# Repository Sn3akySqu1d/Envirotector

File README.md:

Envirotector is a compact, portable weather station that logs data to an SD card and displays temperature, air pressure and humidity data as well as the time on an OLED display.

I decided to make this project as a cool, portable way to track the conditions of different places you visit with the option to export the data via sd card for analysis.

Features:  
5 screens (time, temperature, humidity, air pressure, graph) that are navigaated using a rotary encoder  
Saves recorded data to an SD card every 10 minuites for up to 1 week 
Screen automaticlaly sleeps to save power  
The last screen has a graph that displays the sensor readings over time for the last 24 hours.

[BOM](BOM.csv)
# BOM  

| Component               | Link                                                                                                                                                                                                                                                                                                                                                                                                                                                                                                                                                                                                                                                                                                                                                                                                                                                                                                                                                                                                                                                                                                                                        | Component                  | Link                                                                                                           | Price (USD) |
| -------------------------- | -------------------------------------------------------------------------------------------------------------- | ----------- |
| XIAO RP2040                | [https://www.aliexpress.com/item/1005003682505451.html](https://www.aliexpress.com/item/1005003682505451.html) | 12.11       |
| DHT11 Humidity Sensor      | [https://www.aliexpress.com/item/1005007728845619.html](https://www.aliexpress.com/item/1005007728845619.html) | 5.02        |
| OLED Display               | [https://www.aliexpress.com/item/1005006262908701.html](https://www.aliexpress.com/item/1005006262908701.html) | 3.52        |
| RTC Module                 | [https://www.aliexpress.com/item/1005008352022059.html](https://www.aliexpress.com/item/1005008352022059.html) | 4.83        |
| BMP180 Air Pressure Sensor | [https://www.aliexpress.com/item/1005008474684719.html](https://www.aliexpress.com/item/1005008474684719.html) | 4.03        |
| Rotary Encoder             | [https://www.aliexpress.com/item/1975155185.html](https://www.aliexpress.com/item/1975155185.html)             | 3.62        |
| MicroSD Card Reader        | [https://www.aliexpress.com/item/1005006248599786.html](https://www.aliexpress.com/item/1005006248599786.html) | 2.39        |
| RTC Battery                | [https://www.aliexpress.com/item/1005008363279450.html](https://www.aliexpress.com/item/1005008363279450.html) | 5.90        |
| MicroSD Card               | [https://www.aliexpress.com/item/1005007118463161.html](https://www.aliexpress.com/item/1005007118463161.html) | 1.99        |
| PCB                        | [https://jlcpcb.com](https://jlcpcb.com)                                                                       | 1.50        |
| Case                       | Printed with my own 3D printer                                                                                 | 0.00        |
 total: 44.91 usd

https://youtu.be/wm6Xy655hNI?si=NdGpvTqHyldkWJcv

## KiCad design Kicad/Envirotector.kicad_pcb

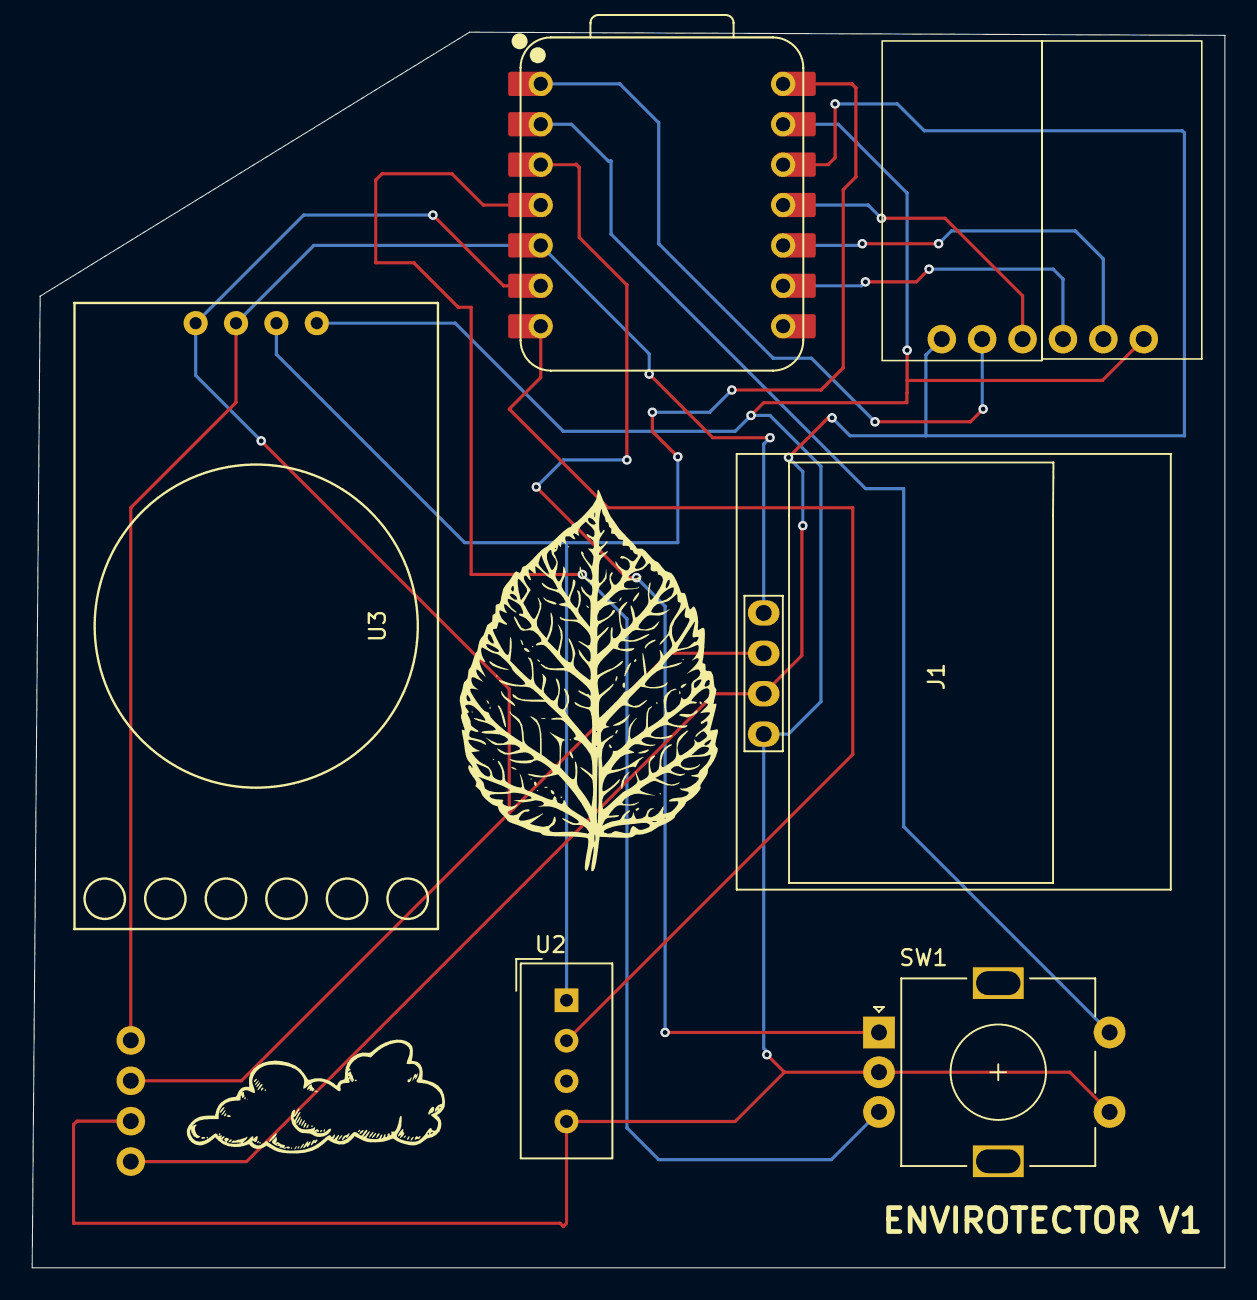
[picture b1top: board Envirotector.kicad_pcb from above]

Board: 2 copper layers, 75.0 x 77.7 mm, 7 parts (0 on the bottom side), 13 nets.

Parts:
J1: OLED Display; 128x64OLED
SW1: RotaryEncoder_Switch; RotaryEncoder_Alps_EC11E-Switch_Vertical_H20mm
U1: XIAO-RP2040-DIP
U2: DHT11; Aosong_DHT11_5.5x12.0_P2.54mm
U3: RTC_DS3231
U4, U5: Untitled

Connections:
+3.3V: J1.3 (VCC), U1.12 (3V3), U4.1 (VCC), U5.2 (VCC)
+5V: U1.14 (VBUS), U2.1 (VDD), U3.3 (VCC)
GND: J1.4 (GND), SW1.C, SW1.S1, U1.13 (GND), U2.4 (GND), U3.4 (GND), U4.2 (GND), U5.1 (GND)
unnamed: J1.1, U1.5 (GPIO6/SDA), U3.2 (SDA), U4.4 (SDA)
unnamed: J1.2, U1.6 (GPIO7/SCL), U3.1 (SCL), U4.3 (SCL)
unnamed: U1.7 (GPIO0/TX), U2.2 (DATA)
unnamed: U1.9 (GPIO2/SCK), U5.5 (SCK)
unnamed: U1.11 (GPIO3/MOSI), U5.4 (MOSI)
unnamed: U1.10 (GPIO4/MISO), U5.3 (MISO)
unnamed: U1.1 (GPIO26/ADC0/A0), U5.6 (CS)
unnamed: SW1.S2, U1.2 (GPIO27/ADC1/A1)
unnamed: SW1.A, U1.3 (GPIO28/ADC2/A2)
unnamed: SW1.B, U1.4 (GPIO29/ADC3/A3)

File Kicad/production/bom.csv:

Designator,Footprint,Quantity,Value,LCSC Part #
J1,128x64OLED,1,OLED Display,
SW1,RotaryEncoder_Alps_EC11E-Switch_Vertical_H20mm,1,RotaryEncoder_Switch,
U1,XIAO-RP2040-DIP,1,XIAO-RP2040-DIP,
U2,Aosong_DHT11_5.5x12.0_P2.54mm,1,DHT11,
U3,RTC_DS3231,1,~,
"U4, U5",Untitled,2,~,

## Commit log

2025-07-02 upload
2025-07-06 updated pcb
2025-07-06 Final
2025-07-06 updated footprint and case for bmp180 breakout board
2025-07-07 added BOM to readme
2025-07-07 updated the sd card reader to breakoutboard
2025-07-08 updated 3.3v xiao output
2025-07-08 regenerated pcb production files
2025-07-08 rerouted pcb and updated silkscreen
2025-07-09 updated microsd card reader
2025-08-06 build completed
2025-08-06 updated readme cad images
